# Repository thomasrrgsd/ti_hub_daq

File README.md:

<h1 align="center">TI Innovator HUB Data Aquisition Tool<br/>Team TI-82<br/>Cameron Dennis, John Douthit, William Jarratt, Christian Offodile</h1>

## Table of Contents

* [Introduction](#introduction)
* [User Guide and Theory of Operation](#user-guide-and-theory-of-operation)
* [Folder Descriptions](#folder-descriptions)
* [Demonstration Videos](#demonstration-videos)
* [Project Pitch](#project-pitch)

## Introduction

### Background
Students often begin learning about electronics in an environment where there is no access to the needed equipment, such as oscilloscopes, logic analyzers, function generators, and multimeters.

### Objective
Our goal was to create an inexpensive add-on for the TI Innovator HUB that provides data acquisition capabilities, with an intuitive web page based graphical user interface that works across many user devices.

### Product Requirements
- 8 Channel logic analyzer
- DMM that measures current, voltage, power, resistance
- 2 Channel oscilloscope
- Sine, square, sawtooth function generator
- Web browser-based GUI
- Wi-Fi Connectivity

### Design Challenges Encountered
- Integrating firmware for each peripheral.
- Optimizing data stream for real time operation.
- Changing firmware to allow peripherals to communicate with each other.
- Improving error checking to prevent hangups.

##  User Guide and Theory of Operation

Please see [this folder](./project_files/).

## Folder Descriptions

- /esp32_firmware: This folder gives the rundown on the wifi module (ESP32). Contains the firmware and instructions on how to upload it to the ESP32 and run it with the TI Innovator HUB.
- /final_gui: This folder shows the code behind the web based GUI. This folder contains instructions on how you can modify the webpages, encode them, and update them on the ESP32.
- /project_files: This folder contains administrative documents such as BOM, budget, project planning, theory of operation, and user manual. It is important to note that how to use the project and how it works is contained in the documents in this folder.
- /schematics: This folder contains the CAD files used to create the PCBs for each module. The PCBs were designed using EagleCAD.
- /ti_innovator_hub_firmware: This folder contains information on the firmware that resides inside the TI Innovator HUB. How the software works is located in the theory of operation document.

## Demonstration Videos

- [Beta Demo Video](https://youtu.be/WWzbL9Egt7U)
- [Final Demo Video](https://www.youtube.com/watch?v=TzPDwndSMNo)

## Project Pitch

### Background of Company: 
Global semiconductor company that designs, manufactures, tests and sells analog and embedded processing chips. Our products help our customers efficiently manage power, accurately sense and transmit data and provide the core control or processing in their designs.

### Problem Background and the need:
Work on building a basic instrumentation tool for portable signal measurements using the classroom ready TI-Innovator Hub product. Create a basic oscilloscope out of a microcontroller for collecting test and measurement data! Over the course of the project, the team will use an existing microcontroller kit and create a GUI interface to showcase wave forms, logic analyzer data, and digital multimeter functions. It is very important for engineers to be able to take measurements when debugging hardware. While benchtop equipment is highly capable, it is not portable and can be very expensive. The best tools are often the ones that are available, so portable tools are always in demand, even if the performance is not the same as professional equipment. The team will create software that works with existing hardware to display information collected from the portable data acquisition tool. They will iterate the design to improve the user “out of box” experience. They will use Whole Product development philosophy to create the necessary marketing materials and software examples to ensure a positive experience with users. The team will also design or research any accessory components that will be included in the final kit, which could include a custom enclosure, connectors, cables, power supplies, stickers, and other necessary parts.

### Problem Description/requirements (List of high-level functionality you expect to see in the end product):
- Software GUI that runs in web browser or as native PC application
- GUI Composer app or HTML5 app
- Functional prototype
- TI-Innovator Hub
- Jumper Wires
- (optional) Additional sensors or peripherals (e.g. DAC, voltmeter)
- (optional) Measurement probes or scope probes
- Programmable by USB from host PC
- Test plan to verify use for academic settings
- Identify and test use cases for basic circuits
- Documentation on user manual and quick start guide
- Include pin map diagram for inputs
- Include color photo of final board
- Explanation of out of box demo or default program
- At least 1 example code samples with documentation
- Measurements displayed in GUI
- Can be based on TI code examples provided for MCU or other sources
- Make available for Code Composer Studio and/or Arduino IDE
- Written list or physical prototypes of accessories for the development board which could include a custom enclosure, connectors, cables, power supplies, stickers, and other necessary parts

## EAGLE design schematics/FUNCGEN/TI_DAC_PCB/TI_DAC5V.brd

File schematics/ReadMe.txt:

List of Files in Folder
* FUNCGEN (Function Generator hardware files)
   * FUNCGENSCH.png (Image of schematic)
   * FUNCGENBRD (Image of board layout)
   * PCB_TI82_FuncGen.zip (Gerber files)
   * TI_DAC_PCB (Eagle design files)
      * TI_DAC5V.brd (Board design file)
      * TI_DAC5V.sch (Schematic design file)
* ESPPCB1 (Wifi Module hardware files 1st iteration)
   * ESPSCH1.png (Image of schematic)
   * ESPPCB1.png (Image of board layout)
   * PCB_TI82_ESP1.zip (Gerber files)
   * TI_ESP_PCB (Eagle design files)
      * TI_ESP_PCB.brd (Board design file)
      * TI_ESP_PCB.sch (Schematic design file)
* ESPPCB2 (Wifi Module hardware files 2nd iteration)
   * ESPSCH2.png (Image of schematic)
   * ESPPCB2.png (Image of board layout)
   * PCB_TI82_ESP2.zip (Gerber files)
   * TI_ESP_PCB2 (Eagle design files)
      * TI_ESP_PCB2.brd (Board design file)
      * TI_ESP_PCB2.sch (Schematic design file)
* MULTIMETER
   * DMMSCH (Image of schematic)
   * DMMPCB (Image of board layout)
   * PCB_TI82_DMM.zip (Gerber files)
   * TI_DMM_PCB (Eagle design files)
      * TI_DMM_PCB.brd (Board design file)
      * TI_DMM_PCB.sch (Schematic design file)

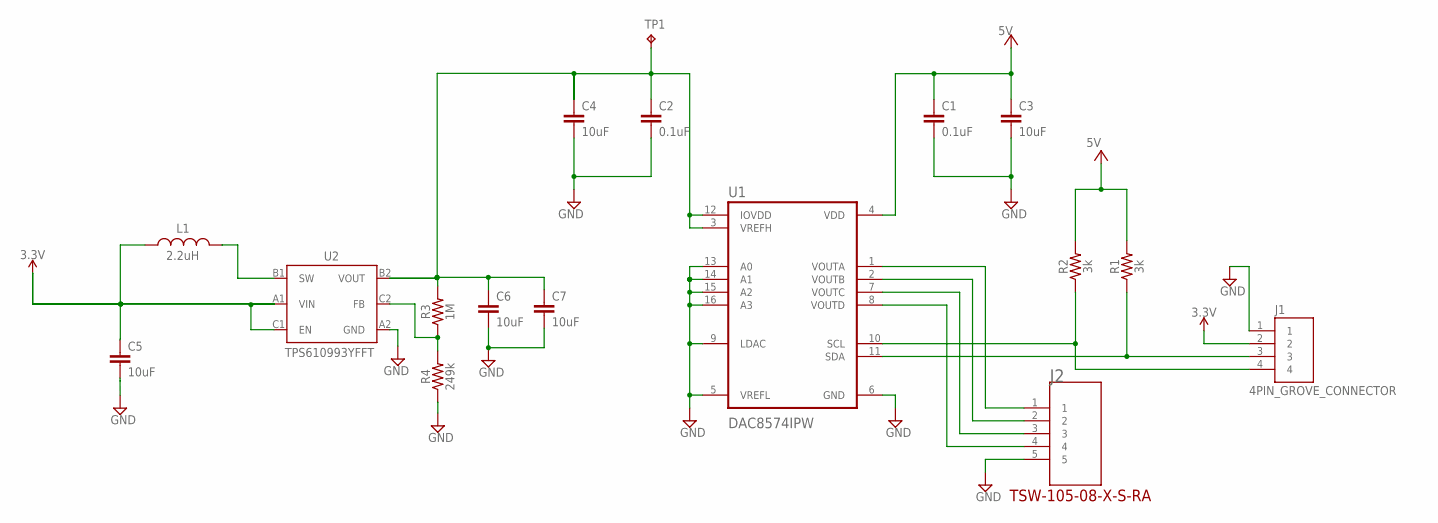
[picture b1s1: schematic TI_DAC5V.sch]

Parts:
C1, C2: 0.1uF; 1206
C3, C4: 10uF; 1206
C5, C6, C7: 10uF; CAPC1608X90N
J1: 4PIN_GROVE_CONNECTOR; SEEED_114020163
J2: TSW-105-08-X-S-RAJ; SAMTEC-TSW-105-08-X-S-RA
L1: 2.2uH; VLS201610CX-2R2M-1
R1, R2: 3k; 1206
R3: 1M; 0603
R4: 249k; 0603
TP1: TPPAD1-13; P1-13
U1: DAC8574IPW; SOP65P640X120-16N
U2: TPS610993YFFT

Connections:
3.3V: C5.1, J1.2, L1.1, U2.A1 (VIN), U2.C1 (EN)
5V: C1.1, C2.1, C3.1, C4.1, C6.1, C7.1, R1.2, R2.2, R3.2, TP1.TP, U1.3 (VREFH), U1.4 (VDD), U1.12 (IOVDD), U2.B2 (VOUT)
FB: R3.1, R4.2, U2.C2 (FB)
GND: C1.2, C2.2, C3.2, C4.2, C5.2, C6.2, C7.2, J1.1, J2.5, R4.1, U1.5 (VREFL), U1.6 (GND), U1.9 (LDAC), U1.13 (A0), U1.14 (A1), U1.15 (A2), U1.16 (A3), U2.A2 (GND)
SCL: J1.4, R2.1, U1.10 (SCL)
SDA: J1.3, R1.1, U1.11 (SDA)
SW: L1.2, U2.B1 (SW)
VOUTA: J2.1, U1.1 (VOUTA)
VOUTB: J2.2, U1.2 (VOUTB)
VOUTC: J2.3, U1.7 (VOUTC)
VOUTD: J2.4, U1.8 (VOUTD)

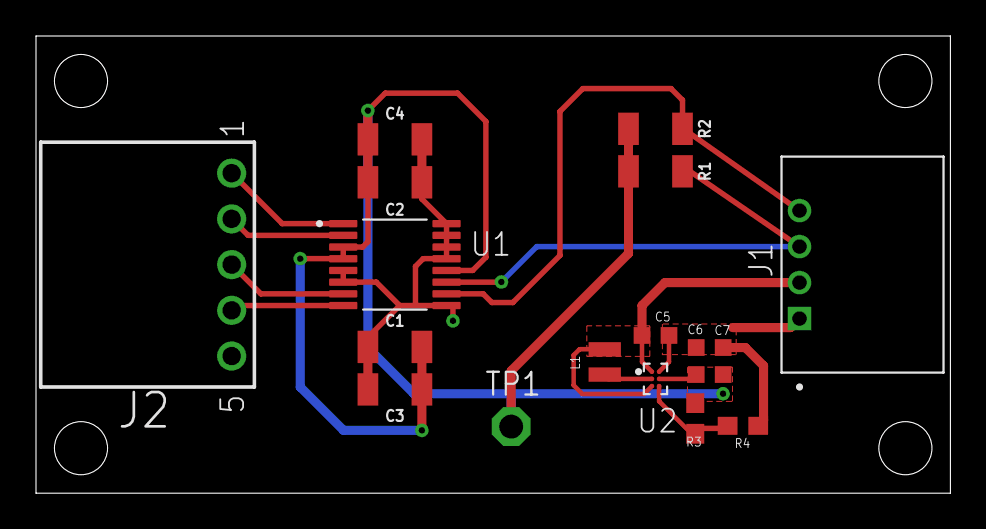
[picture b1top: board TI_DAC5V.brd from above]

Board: 2 copper layers, 50.8 x 25.4 mm, 17 parts (0 on the bottom side), 11 nets.

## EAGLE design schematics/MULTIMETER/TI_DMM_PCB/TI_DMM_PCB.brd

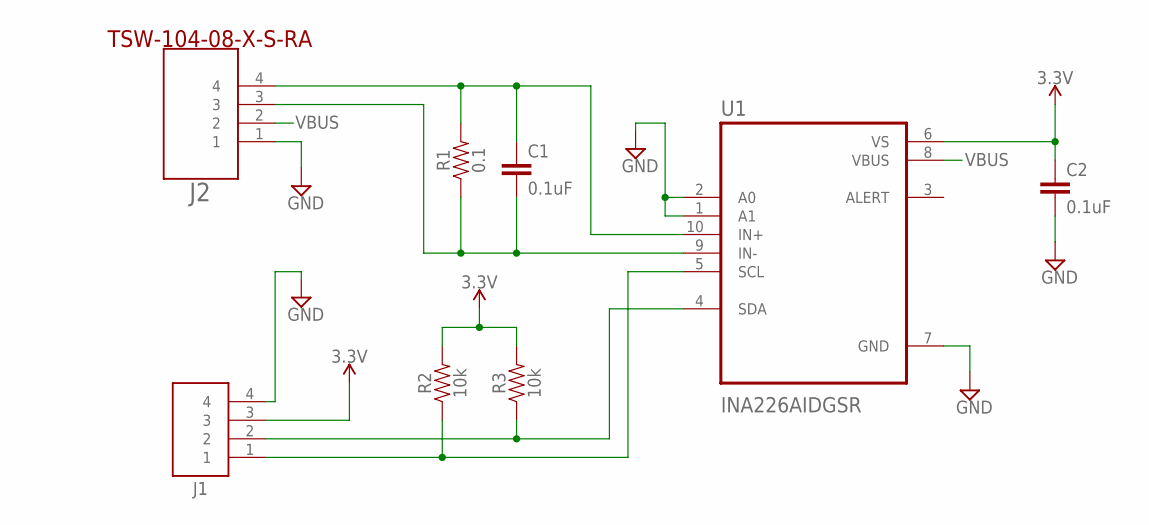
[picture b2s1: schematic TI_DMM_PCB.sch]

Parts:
C1, C2: 0.1uF; 0603
J1: 4PIN_GROVE_CONNECTOR; SEEED_114020163
J2: TSW-104-08-X-S-RAJ; SAMTEC-TSW-104-08-X-S-RA
R1: 0.1; 0603
R2, R3: 10k; 0603
U1: INA226AIDGSR; SOP50P490X110-10N

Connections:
3.3V: C2.1, J1.3, R2.2, R3.2, U1.6 (VS)
GND: C2.2, J1.4, J2.1, U1.1 (A1), U1.2 (A0), U1.7 (GND)
IN+: C1.1, J2.4, R1.2, U1.10 (IN+)
IN-: C1.2, J2.3, R1.1, U1.9 (IN-)
SCL: J1.1, R2.1, U1.5 (SCL)
SDA: J1.2, R3.1, U1.4 (SDA)
VBUS: J2.2, U1.8 (VBUS)

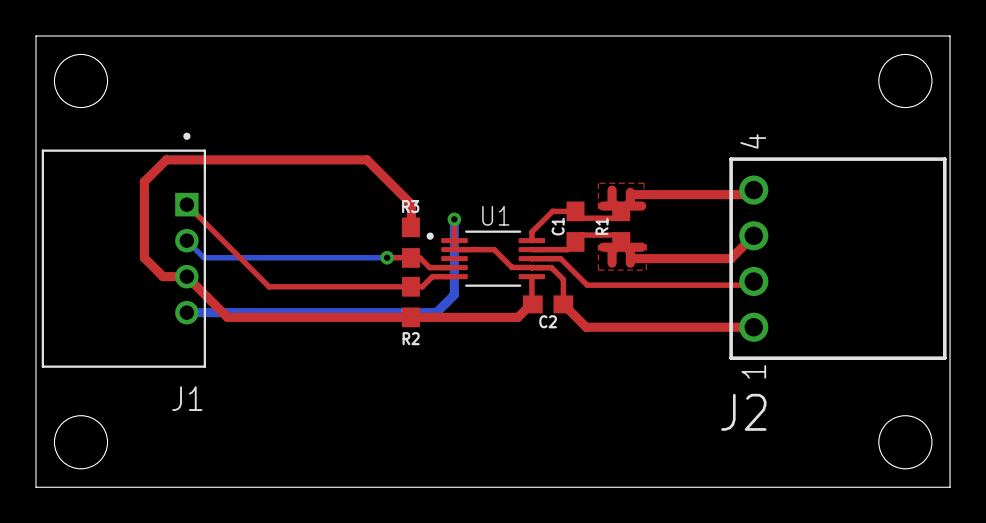
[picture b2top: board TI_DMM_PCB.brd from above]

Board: 2 copper layers, 50.8 x 25.1 mm, 8 parts (0 on the bottom side), 7 nets.

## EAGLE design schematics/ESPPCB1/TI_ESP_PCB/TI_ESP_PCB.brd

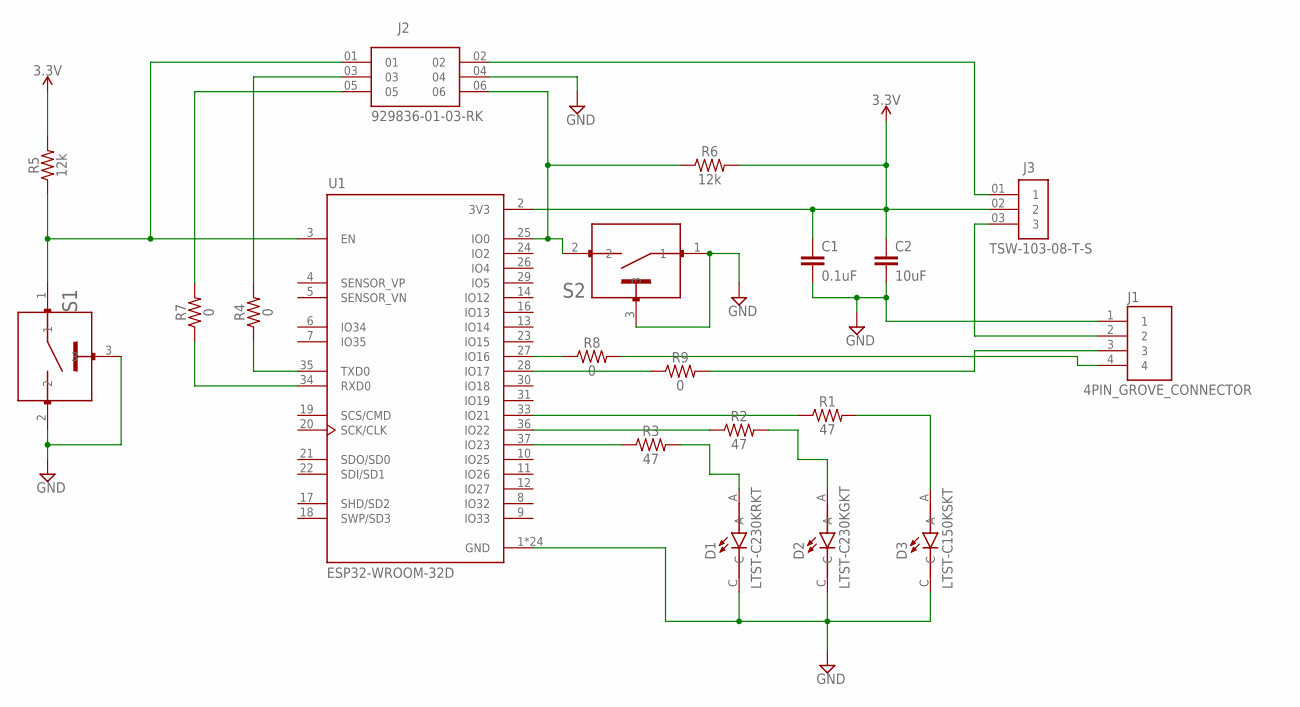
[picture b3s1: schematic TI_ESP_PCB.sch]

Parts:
C1: 0.1uF; 1206
C2: 10uF; 1206
D1: LTST-C230KRKT; LEDC3216X110
D2: LTST-C230KGKT; LEDC3216X110
D3: LTST-C150KSKT; LEDC3216X110
J1: 4PIN_GROVE_CONNECTOR; SEEED_114020163
J2: 929836-01-03-RK; 3M-2X3_6PIN_CONNECTOR
J3: TSW-103-08-T-S; SAMTEC_TSW-103-08-T-S
R1, R2, R3: 47; 1206
R4, R7, R8, R9: 0; 1206
R5, R6: 12k; 1206
S1, S2: B3U-1100P; SW_B3U-1100P
U1: ESP32-WROOM-32D; MODULE_ESP32-WROOM-32D

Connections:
3.3V: C1.1, C2.1, J3.02 (2), R5.2, R6.2, U1.2 (3V3)
EN: J2.01, R5.1, S1.1, U1.3 (EN)
GND: C1.2, C2.2, D1.C, D2.C, D3.C, J1.1, J2.04, S1.2, S1.3, S2.1, S2.3, U1.1 (GND), U1.15 (GND), U1.38 (GND), U1.39_1 (GND), U1.39_2 (GND), U1.39_3 (GND), U1.39_4 (GND), U1.39_5 (GND), U1.39_6 (GND), U1.39_7 (GND), U1.39_8 (GND), U1.39_9 (GND), U1.39_10 (GND), U1.39_11 (GND), U1.39_12 (GND), U1.39_13 (GND), U1.39_14 (GND), U1.39_15 (GND), U1.39_16 (GND), U1.39_17 (GND), U1.39_18 (GND), U1.39_19 (GND), U1.39_20 (GND), U1.39_21 (GND)
IO0: J2.06, R6.1, S2.2, U1.25 (IO0)
IO16: R8.1, U1.27 (IO16)
IO17: R9.1, U1.28 (IO17)
IO21: R1.1, U1.33 (IO21)
IO22: R2.1, U1.36 (IO22)
IO23: R3.1, U1.37 (IO23)
unnamed: J2.03, R4.2
unnamed: J1.2, J3.03 (3)
unnamed: J2.02, J3.01 (1)
unnamed: D1.A, R3.2
unnamed: D2.A, R2.2
unnamed: D3.A, R1.2
unnamed: J1.4, R8.2
unnamed: J1.3, R9.2
unnamed: J2.05, R7.2
RXD0: R7.1, U1.34 (RXD0)
TXD0: R4.1, U1.35 (TXD0)

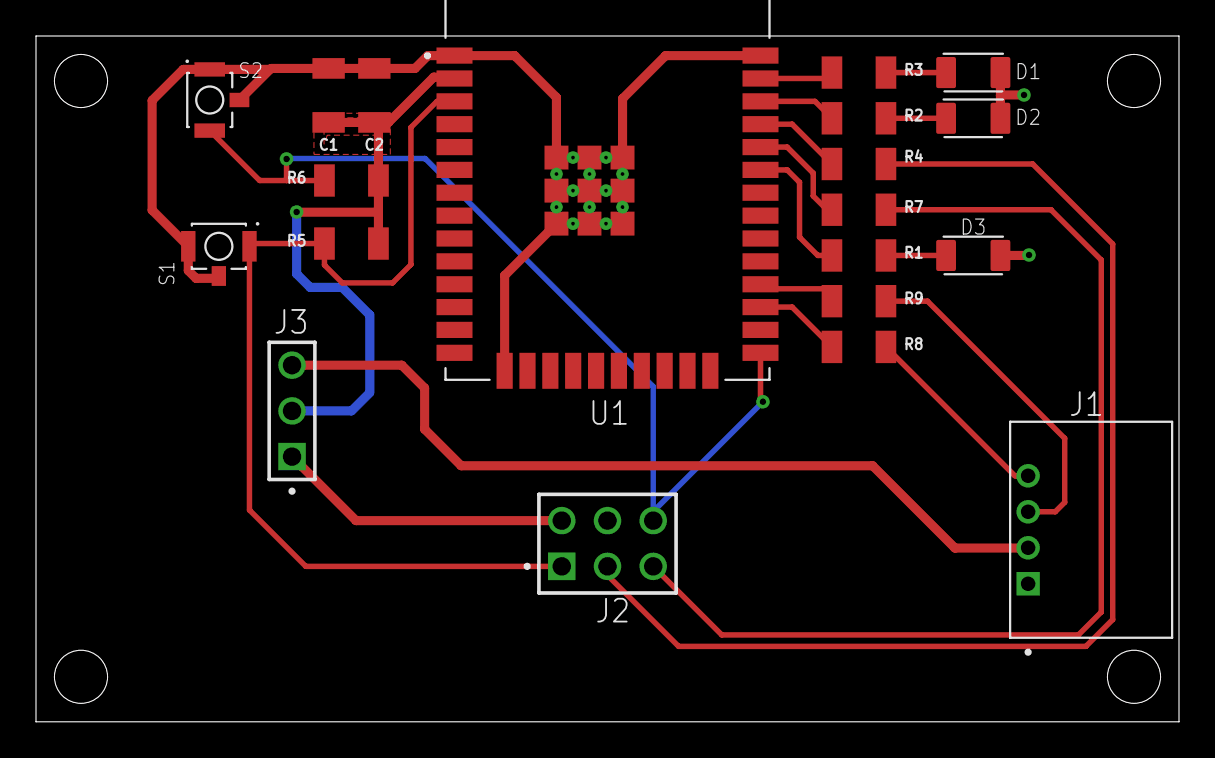
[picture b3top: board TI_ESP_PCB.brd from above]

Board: 2 copper layers, 63.5 x 38.1 mm, 20 parts (0 on the bottom side), 20 nets.

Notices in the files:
parts and their libraries:
SparkFun-PowerSymbols: Licensing: Creative Commons ShareAlike 4.0 International - https://creativecommons.org/licenses/by-sa/4.0
